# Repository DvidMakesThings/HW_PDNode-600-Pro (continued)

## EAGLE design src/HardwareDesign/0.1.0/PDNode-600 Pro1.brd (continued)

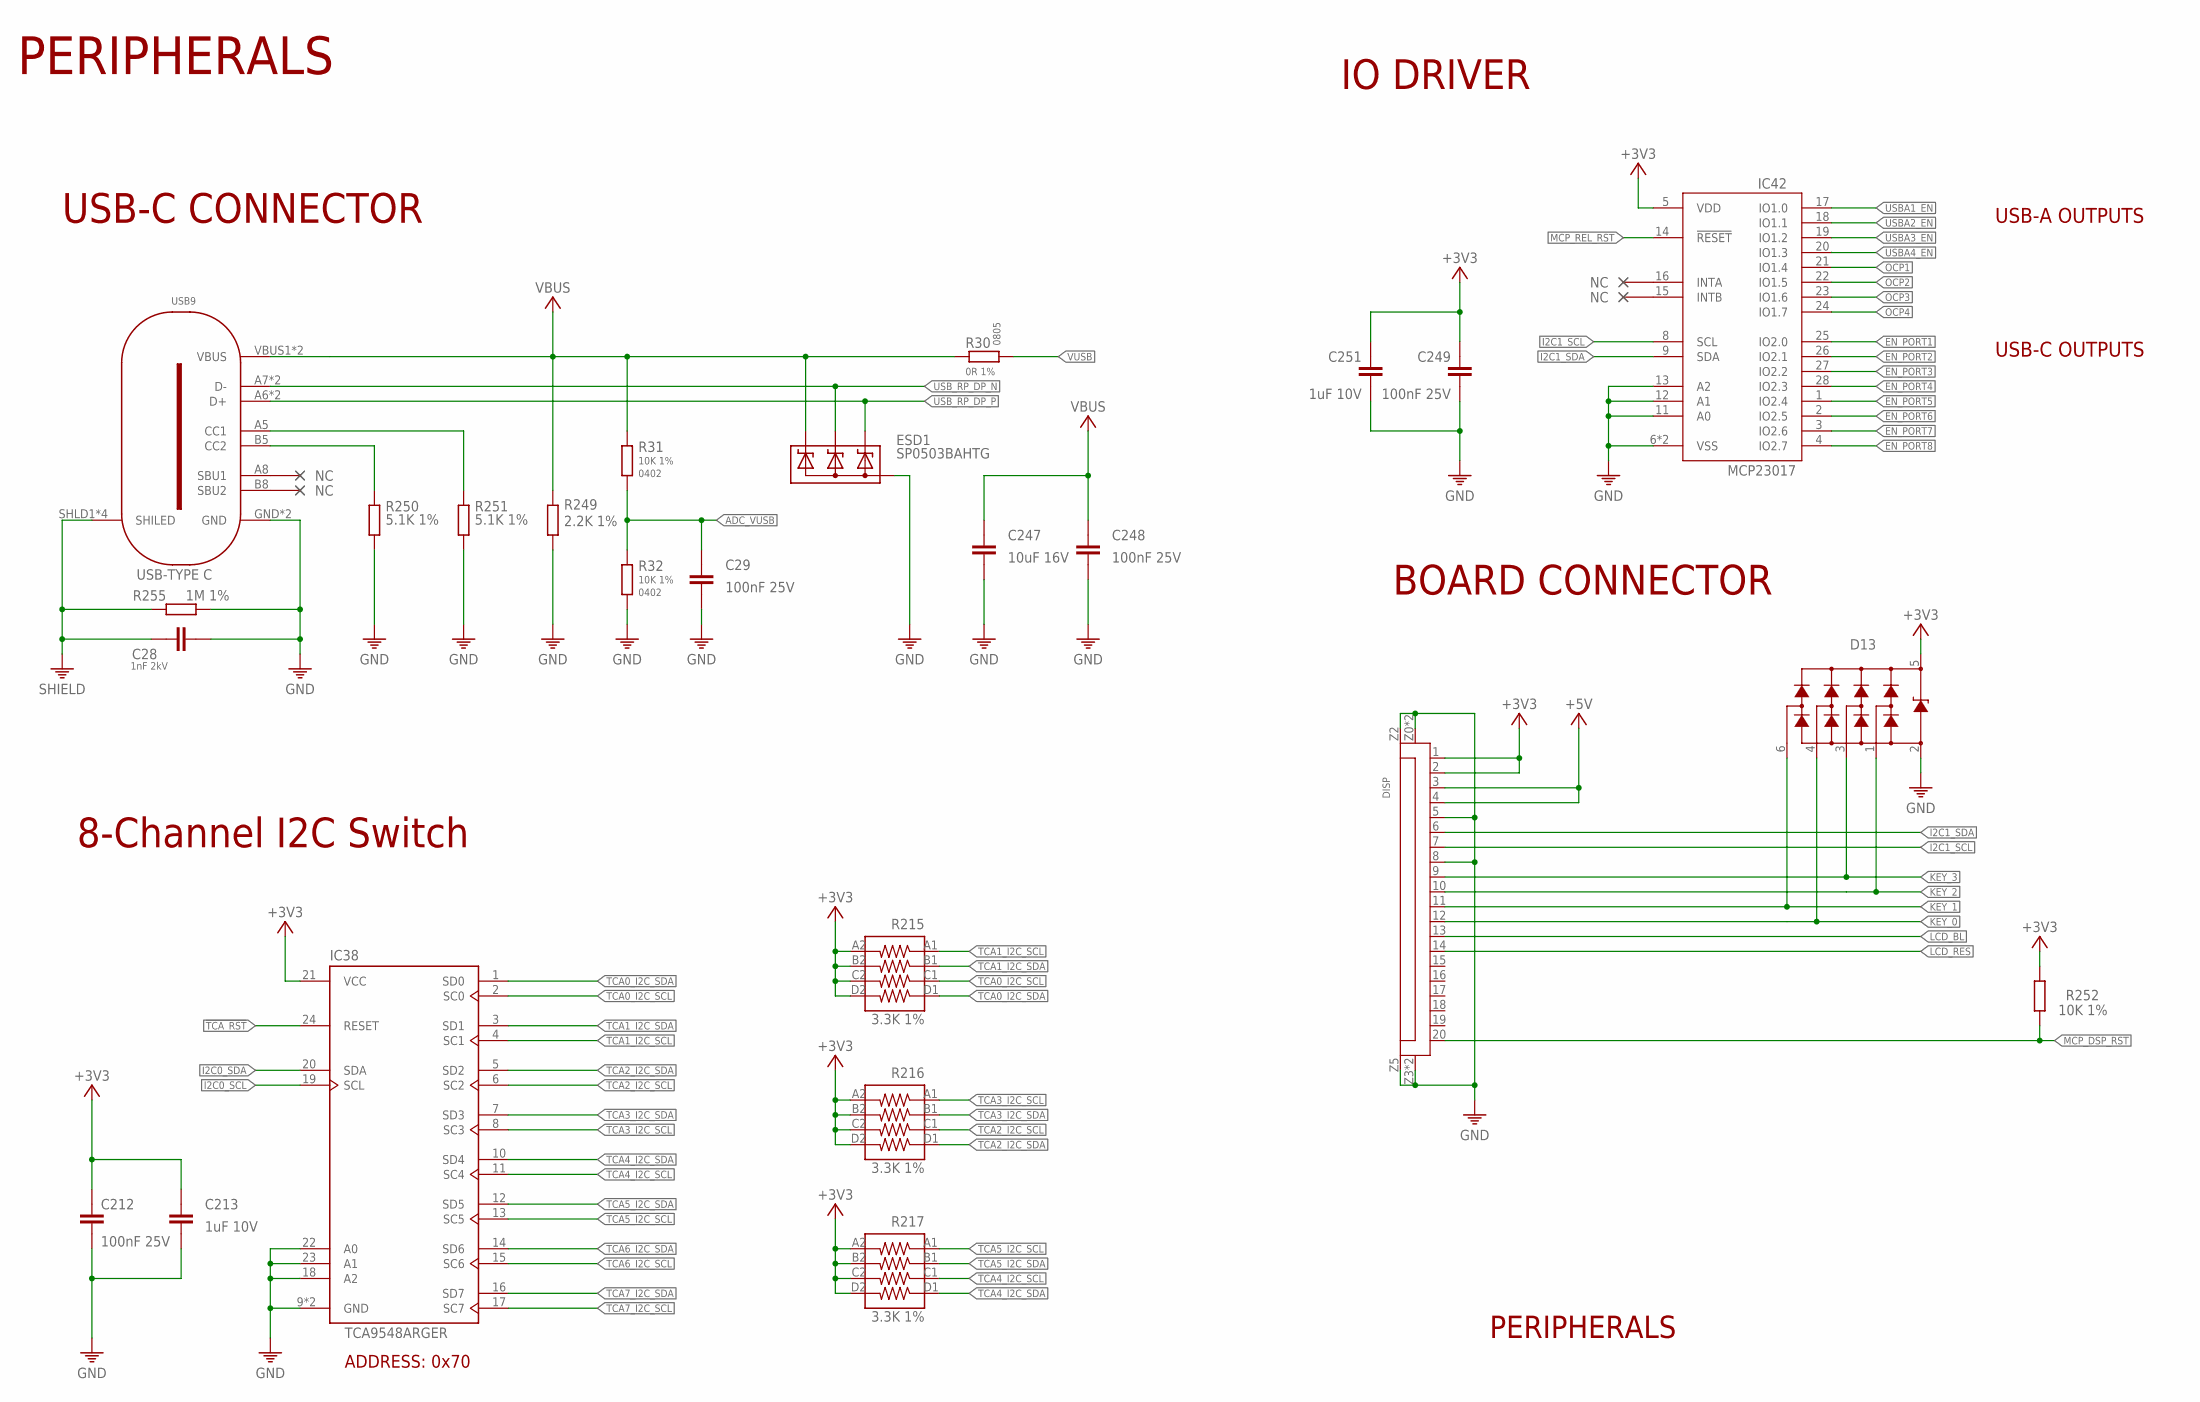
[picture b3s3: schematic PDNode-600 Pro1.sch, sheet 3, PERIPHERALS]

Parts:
C28: 1nF 2kV; 1206
C29, C248: 100nF 25V; 0402
C212, C249: 100nF 25V; 0201
C213, C251: 1uF 10V; 0201
C247: 10uF 16V; 0603
D13: HDMIULC6-4SC6Y; SOT23-6
DISP: AFC11-S20ICC-00; FPC20
ESD1: SP0503BAHTG; SOT143
IC38: TCA9548ARGER; QFN50P400X400X100-25T210N
IC42: MCP23017T-E/ML; QFN28[6X6]ML
R30: 0R 1%; 0805
R31, R32: 10K 1%; 0402
R215, R216, R217: 3.3K 1%; _0603X4-1206
R249: 2.2K 1%; 0201
R250, R251: 5.1K 1%; 0201
R252: 10K 1%; 0201
R255: 1M 1%; 1206
USB9: USB-TYPE-C-018; USB-C

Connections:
!TCA_RST: IC38.24 (RESET)
+3V3: C212.1, C213.1, C249.1, C251.1, D13.5, DISP.1, DISP.2, IC38.21 (VCC), IC42.5 (VDD), R215.A2 (8), R215.B2 (7), R215.C2 (6), R215.D2 (5), R216.A2 (8), R216.B2 (7), R216.C2 (6), R216.D2 (5), R217.A2 (8), R217.B2 (7), R217.C2 (6), R217.D2 (5), R252.2; also elsewhere on the board
+5V: DISP.3, DISP.4
ADC_VUSB: C29.1, R31.2, R32.1
CC1: R251.1, USB9.A5 (CC1)
CC2: R250.1, USB9.B5 (CC2)
EN_PORT1: IC42.25 (IO2.0); also elsewhere on the board
EN_PORT2: IC42.26 (IO2.1); also elsewhere on the board
EN_PORT3: IC42.27 (IO2.2); also elsewhere on the board
EN_PORT4: IC42.28 (IO2.3); also elsewhere on the board
EN_PORT5: IC42.1 (IO2.4); also elsewhere on the board
EN_PORT6: IC42.2 (IO2.5); also elsewhere on the board
EN_PORT7: IC42.3 (IO2.6); also elsewhere on the board
EN_PORT8: IC42.4 (IO2.7); also elsewhere on the board
GND: C28.2, C29.2, C212.2, C213.2, C247.2, C248.2, C249.2, C251.2, D13.2, DISP.5, DISP.8, DISP.Z0 (Z1), DISP.Z1, DISP.Z2, DISP.Z3, DISP.Z4 (Z3), DISP.Z5 (Z4), ESD1.1 (A), IC38.9 (GND), IC38.18 (A2), IC38.22 (A0), IC38.23 (A1), IC38.25 (GND), IC42.6 (VSS), IC42.11 (A0), IC42.12 (A1), IC42.13 (A2), IC42.PAD (VSS), R32.2, R249.2, R250.2, R251.2, R255.2, USB9.GND, USB9.GND2 (GND); also elsewhere on the board
I2C0_SCL: IC38.19 (SCL); also elsewhere on the board
I2C0_SDA: IC38.20 (SDA); also elsewhere on the board
I2C1_SCL: DISP.7, IC42.8 (SCL); also elsewhere on the board
I2C1_SDA: DISP.6, IC42.9 (SDA); also elsewhere on the board
KEY_0: D13.4, DISP.12; also elsewhere on the board
KEY_1: D13.6, DISP.11; also elsewhere on the board
KEY_2: D13.1, DISP.10; also elsewhere on the board
KEY_3: D13.3, DISP.9; also elsewhere on the board
LCD_BL: DISP.13
LCD_RES: DISP.14
MCP_DSP_RST: DISP.20, R252.1
MCP_REL_RST: IC42.14 (!RESET)
OCP1: IC42.21 (IO1.4); also elsewhere on the board
OCP2: IC42.22 (IO1.5); also elsewhere on the board
OCP3: IC42.23 (IO1.6); also elsewhere on the board
OCP4: IC42.24 (IO1.7); also elsewhere on the board
SHIELD: C28.1, R255.1, USB9.SHLD1 (SHILED), USB9.SHLD2 (SHILED), USB9.SHLD3 (SHILED), USB9.SHLD4 (SHILED); also elsewhere on the board
TCA0_I2C_SCL: IC38.2 (SC0), R215.C1 (3); also elsewhere on the board
TCA0_I2C_SDA: IC38.1 (SD0), R215.D1 (4); also elsewhere on the board
TCA1_I2C_SCL: IC38.4 (SC1), R215.A1 (1); also elsewhere on the board
TCA1_I2C_SDA: IC38.3 (SD1), R215.B1 (2); also elsewhere on the board
TCA2_I2C_SCL: IC38.6 (SC2), R216.C1 (3); also elsewhere on the board
TCA2_I2C_SDA: IC38.5 (SD2), R216.D1 (4); also elsewhere on the board
TCA3_I2C_SCL: IC38.8 (SC3), R216.A1 (1); also elsewhere on the board
TCA3_I2C_SDA: IC38.7 (SD3), R216.B1 (2); also elsewhere on the board
TCA4_I2C_SCL: IC38.11 (SC4), R217.C1 (3); also elsewhere on the board
TCA4_I2C_SDA: IC38.10 (SD4), R217.D1 (4); also elsewhere on the board
TCA5_I2C_SCL: IC38.13 (SC5), R217.A1 (1); also elsewhere on the board
TCA5_I2C_SDA: IC38.12 (SD5), R217.B1 (2); also elsewhere on the board
TCA6_I2C_SCL: IC38.15 (SC6)
TCA6_I2C_SDA: IC38.14 (SD6)
TCA7_I2C_SCL: IC38.17 (SC7)
TCA7_I2C_SDA: IC38.16 (SD7)
USBA1_EN: IC42.17 (IO1.0); also elsewhere on the board
USBA2_EN: IC42.18 (IO1.1); also elsewhere on the board
USBA3_EN: IC42.19 (IO1.2); also elsewhere on the board
USBA4_EN: IC42.20 (IO1.3); also elsewhere on the board
USB_RP_DP_N: ESD1.3 (C2), USB9.A7 (D-), USB9.B7 (D-); also elsewhere on the board
USB_RP_DP_P: ESD1.2 (C1), USB9.A6 (D+), USB9.B6 (D+); also elsewhere on the board
VBUS: C247.1, C248.1, ESD1.4 (C3), R30.1, R31.1, R249.1, USB9.VBUS1 (VBUS), USB9.VBUS2 (VBUS)
VUSB: R30.2

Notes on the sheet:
PERIPHERALS
USB-C CONNECTOR
8-Channel I2C Switch
ADDRESS: 0x70
IO DRIVER
USB-A OUTPUTS
USB-C OUTPUTS
BOARD CONNECTOR

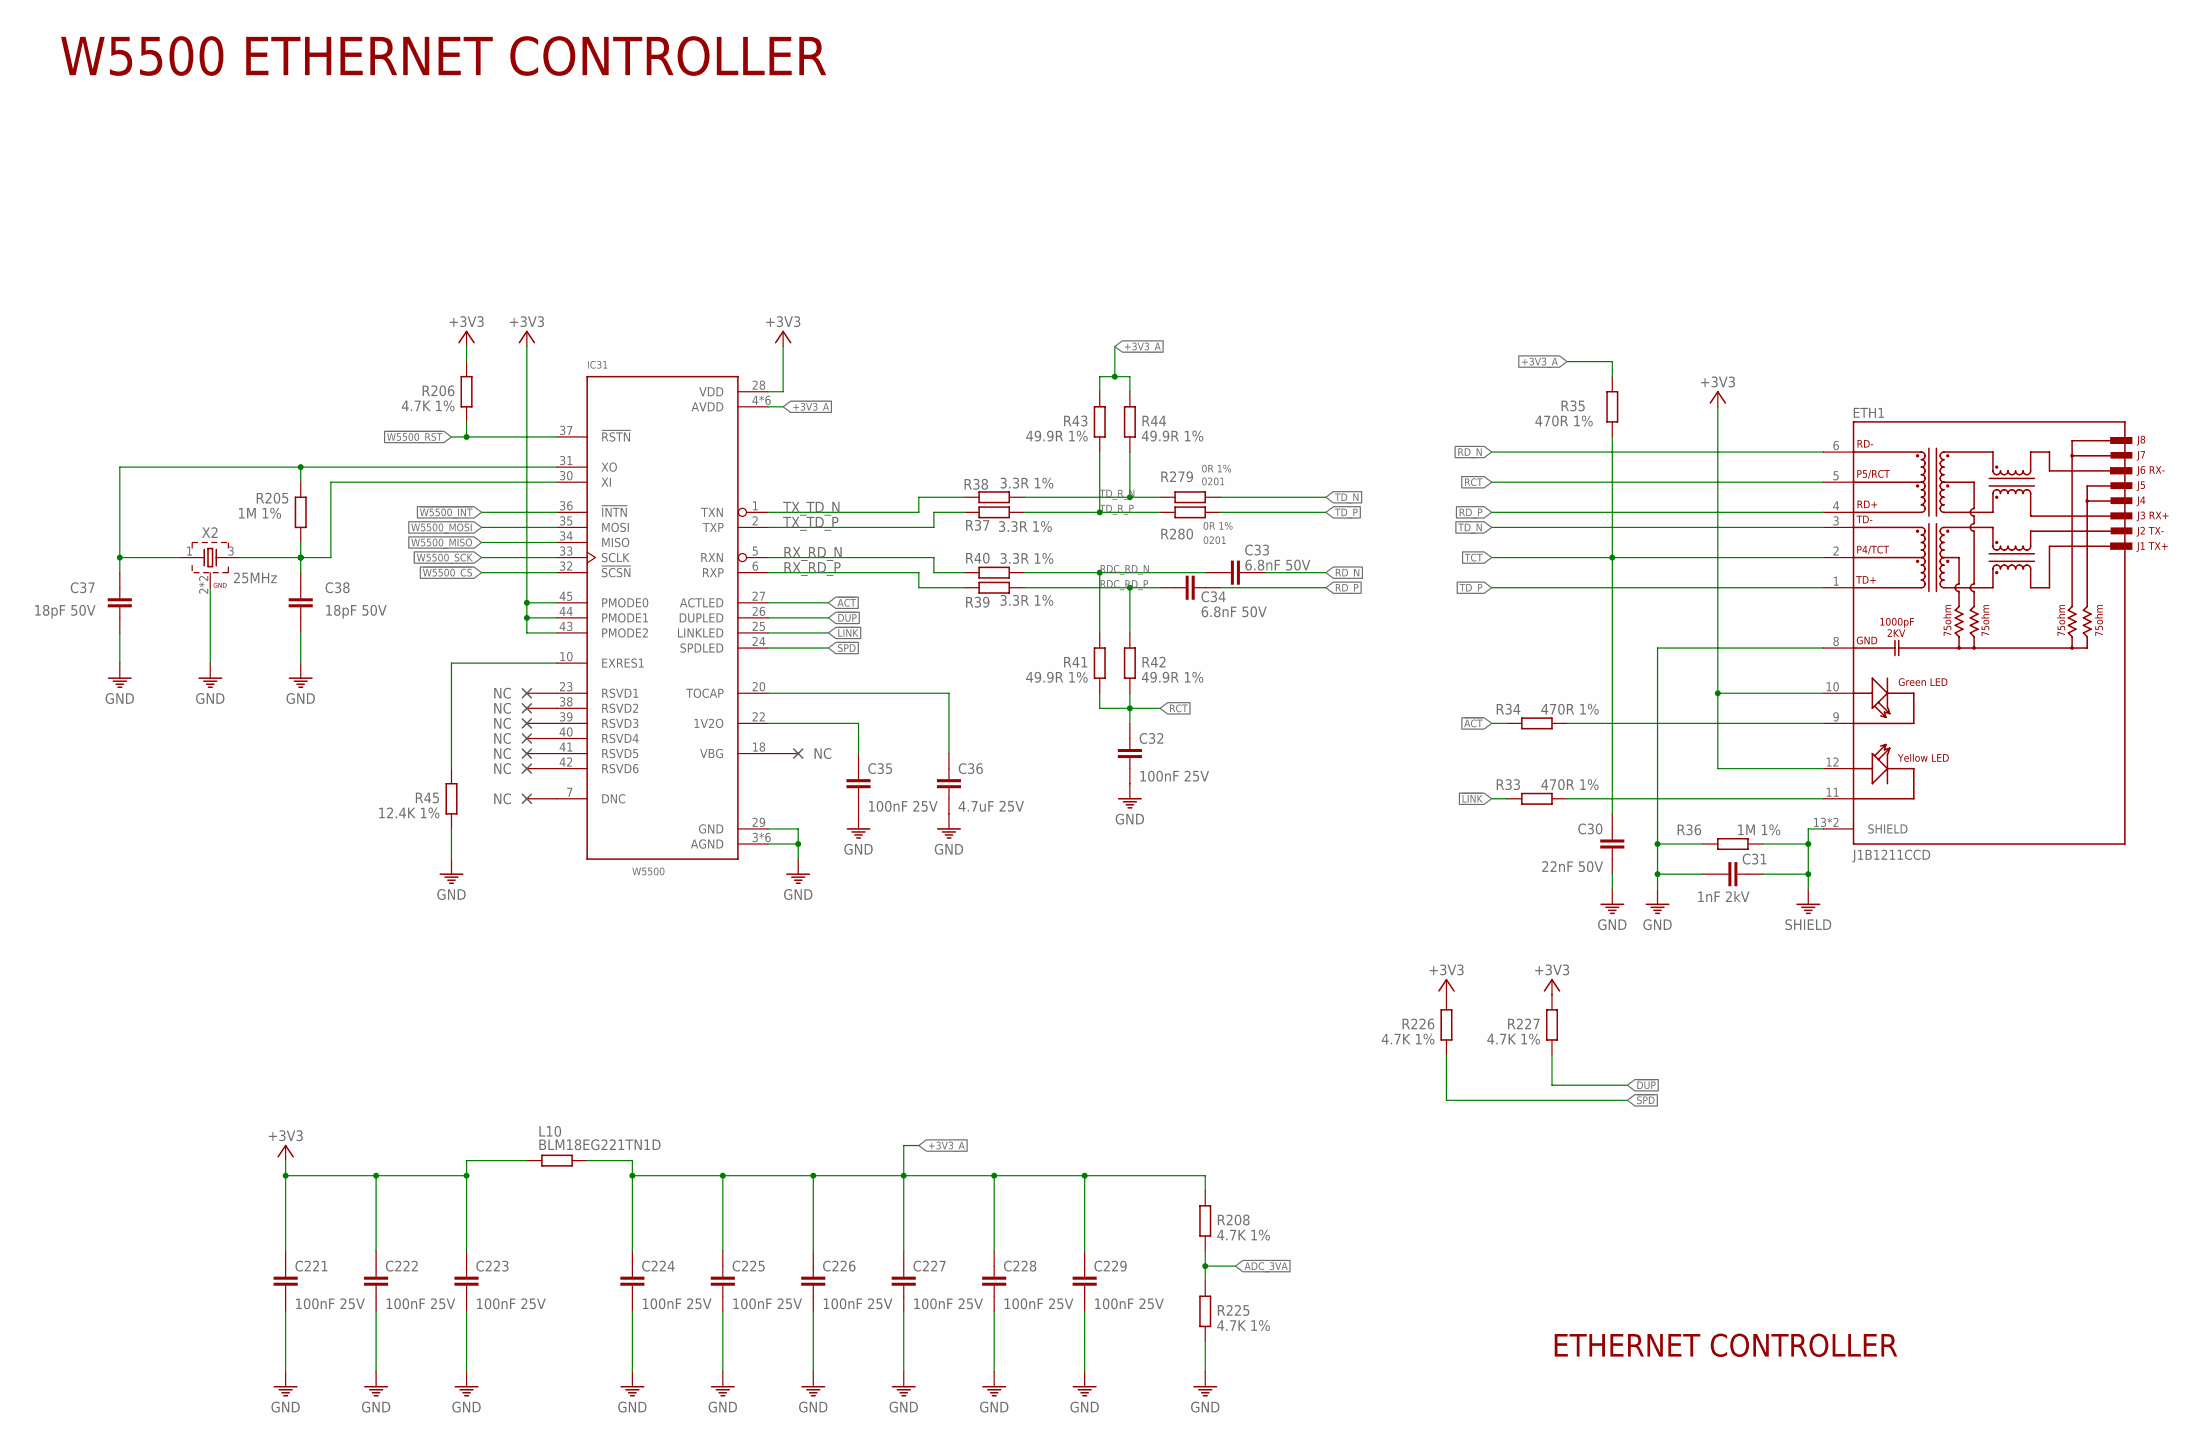
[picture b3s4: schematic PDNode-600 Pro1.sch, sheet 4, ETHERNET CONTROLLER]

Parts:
C30: 22nF 50V; 0402
C31: 1nF 2kV; 1206
C32: 100nF 25V; 0402
C33, C34: 6.8nF 50V; 0201
C35, C221, C222, C223, C224, C225, C226, C227, C228, C229: 100nF 25V; 0201
C36: 4.7uF 25V; 0402
C37, C38: 18pF 50V; 0201
ETH1: J1B1211CCD
IC31: W5500; LQFP48
L10: BLM18EG221TN1D; 0603
R33, R34, R35: 470R 1%; 0402
R36: 1M 1%; 1206
R37, R38, R39, R40: 3.3R 1%; 0201
R41, R42, R43, R44: 49.9R 1%; 0201
R45: 12.4K 1%; R0201
R205: 1M 1%; 0201
R206, R208, R225, R226, R227: 4.7K 1%; 0201
R279, R280: 0R 1%; 0201
X2: 25MHz; WE-XTAL_CFPX-180

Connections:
!ACT: IC31.27 (ACTLED), R34.1
!DUP: IC31.26 (DUPLED), R227.1
!LINK: IC31.25 (LINKLED), R33.1
!SPD: IC31.24 (SPDLED), R226.1
!W5500_CS: IC31.32 (!SCSN); also elsewhere on the board
!W5500_INT: IC31.36 (!INTN); also elsewhere on the board
!W5500_RST: IC31.37 (!RSTN), R206.1; also elsewhere on the board
+3V3: C221.1, C222.1, C223.1, ETH1.10 (GREEN+), ETH1.12 (YELLOW+), IC31.28 (VDD), IC31.43 (PMODE2), IC31.44 (PMODE1), IC31.45 (PMODE0), L10.1, R206.2, R226.2, R227.2; also elsewhere on the board
+3V3_A: C224.1, C225.1, C226.1, C227.1, C228.1, C229.1, IC31.4 (AVDD), IC31.8 (AVDD), IC31.11 (AVDD), IC31.15 (AVDD), IC31.17 (AVDD), IC31.21 (AVDD), L10.2, R35.2, R43.2, R44.2, R208.2
ADC_3VA: R208.1, R225.2
GND: C30.2, C31.1, C32.2, C35.2, C36.2, C37.2, C38.2, C221.2, C222.2, C223.2, C224.2, C225.2, C226.2, C227.2, C228.2, C229.2, ETH1.8 (GND), IC31.3 (AGND), IC31.9 (AGND), IC31.14 (AGND), IC31.16 (AGND), IC31.19 (AGND), IC31.29 (GND), IC31.48 (AGND), R36.1, R45.1, R225.1, X2.2 (GND), X2.4 (GND); also elsewhere on the board
unnamed: ETH1.11 (YELLOW-), R33.2
unnamed: ETH1.9 (GREEN-), R34.2
unnamed: IC31.10 (EXRES1), R45.2
unnamed: C35.1, IC31.22 (1V2O)
unnamed: C36.1, IC31.20 (TOCAP)
unnamed: C38.1, IC31.30 (XI), R205.1, X2.3 (2)
RCT: C32.1, ETH1.5 (P5/RCT), R41.1, R42.1
RDC_RD_N: C33.1, R40.2, R41.2
RDC_RD_P: C34.1, R39.2, R42.2
RD_N: C33.2, ETH1.6 (RD-)
RD_P: C34.2, ETH1.4 (RD+)
RX_RD_N: IC31.5 (RXN), R40.1
RX_RD_P: IC31.6 (RXP), R39.1
SHIELD: C31.2, ETH1.13 (SHIELD), ETH1.14 (SHIELD), R36.2; also elsewhere on the board
TCT: C30.1, ETH1.2 (P4/TCT), R35.1
TD_N: ETH1.3 (TD-), R279.2
TD_P: ETH1.1 (TD+), R280.2
TD_R_N: R38.2, R44.1, R279.1
TD_R_P: R37.2, R43.1, R280.1
TX_TD_N: IC31.1 (TXN), R38.1
TX_TD_P: IC31.2 (TXP), R37.1
W5500_MISO: IC31.34 (MISO); also elsewhere on the board
W5500_MOSI: IC31.35 (MOSI); also elsewhere on the board
W5500_SCK: IC31.33 (SCLK); also elsewhere on the board
XO: C37.1, IC31.31 (XO), R205.2, X2.1

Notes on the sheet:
W5500 ETHERNET CONTROLLER
ETHERNET CONTROLLER

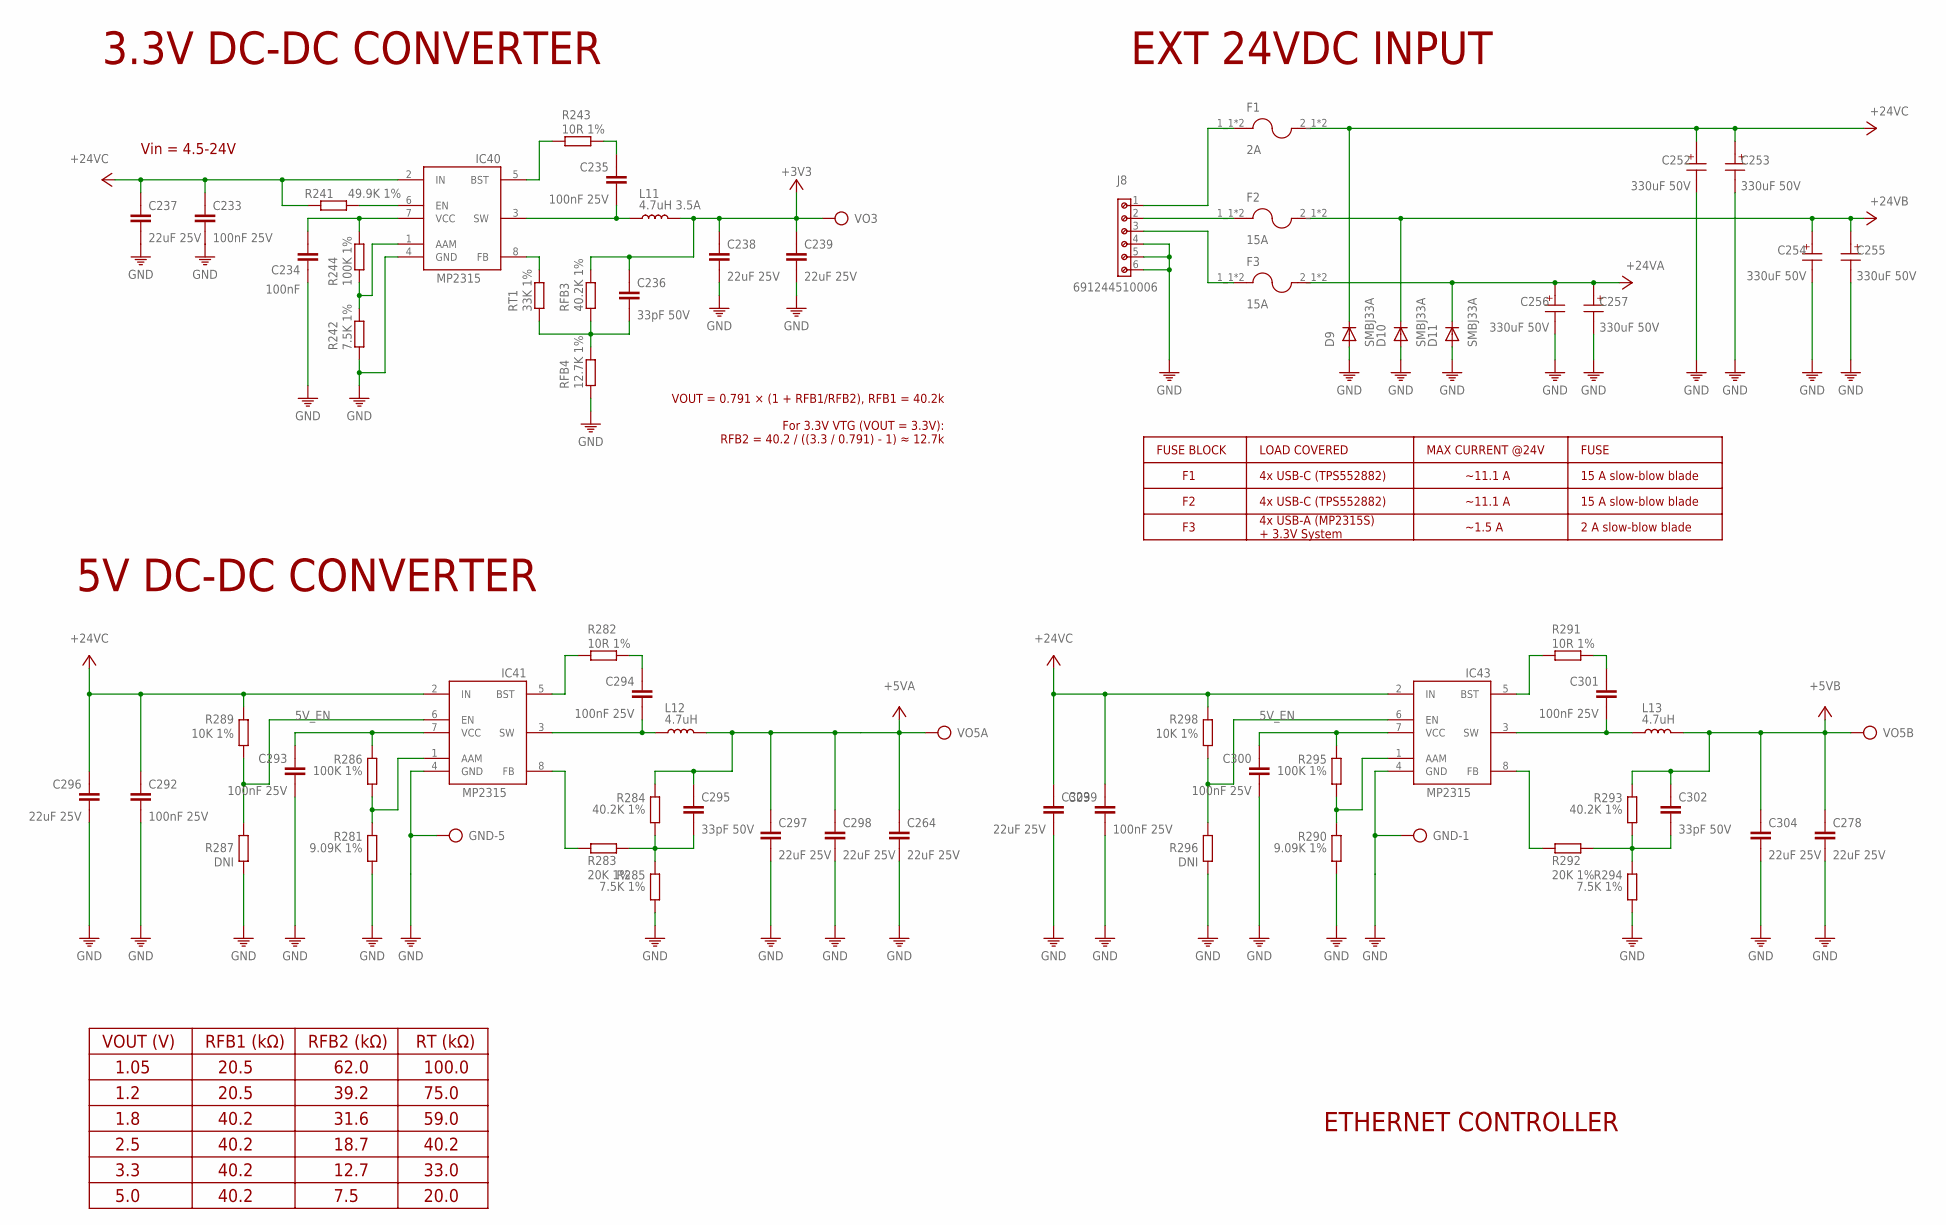
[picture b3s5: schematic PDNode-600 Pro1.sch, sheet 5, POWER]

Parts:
C233, C235: 100nF 25V; 0201
C234: 100nF; 0201
C236: 33pF 50V; 0201
C237, C238, C239, C264, C278, C296, C297, C298, C303, C304: 22uF 25V; 1206
C252, C253, C254, C255, C256, C257: 330uF 50V; 10X10.5(DXL)
C292, C293, C294, C299, C300, C301: 100nF 25V; 0402
C295, C302: 33pF 50V; 0402
D9, D10, D11: SMBJ33A; SMB
F1: 2A; FUSE_3544-2
F2, F3: 15A; FUSE_3544-2
GND-1, GND-5: DNI; TP-ROUND
IC40, IC41, IC43: MP2315GJ-Z; SOT65P280X110-8N
J8: 691244510006
L11: 4.7uH 3.5A; SRR5228A
L12, L13: 4.7uH; SRR5228A
R241: 49.9K 1%; 0201
R242: 7.5K 1%; 0201
R243: 10R 1%; 0201
R244: 100K 1%; 0201
R281, R290: 9.09K 1%; 0402
R282, R291: 10R 1%; 0402
R283, R292: 20K 1%; 0402
R284, R293: 40.2K 1%; 0402
R285, R294: 7.5K 1%; 0402
R286, R295: 100K 1%; 0402
R287, R296: DNI; 0402
R289, R298: 10K 1%; 0402
RFB3: 40.2K 1%; 0201
RFB4: 12.7K 1%; 0201
RT1: 33K 1%; 0201
VO3, VO5A, VO5B: DNI; TP-ROUND

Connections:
3V3_EN_SYS1: IC40.6 (EN), R241.2
5VFB: C295.2, R283.2, R284.2, R285.1
5VFB1: C302.2, R292.2, R293.2, R294.1
5V_EN: IC41.6 (EN), IC43.6 (EN), R287.2, R289.1, R296.2, R298.1
24VINA: F2.1_1 (1), F2.1_2 (1), J8.2
24VINB: F3.1_1 (1), F3.1_2 (1), J8.3
24VINC: F1.1_1 (1), F1.1_2 (1), J8.1
+3V3: C236.1, C238.1, C239.1, L11.2, RFB3.1, VO3.TP; also elsewhere on the board
+5VA: C264.1, C295.1, C297.1, C298.1, L12.2, R284.1, VO5A.TP; also elsewhere on the board
+5VB: C278.1, C302.1, C304.1, L13.2, R293.1, VO5B.TP; also elsewhere on the board
+24V_A: C256.1 (+), C257.1 (+), D11.C, F3.2_1 (2), F3.2_2 (2); also elsewhere on the board
+24V_B: C254.1 (+), C255.1 (+), D10.C, F2.2_1 (2), F2.2_2 (2); also elsewhere on the board
+24V_C: C233.1, C237.1, C252.1 (+), C253.1 (+), C292.1, C296.1, C299.1, C303.1, D9.C, F1.2_1 (2), F1.2_2 (2), IC40.2 (IN), IC41.2 (IN), IC43.2 (IN), R241.1, R289.2, R298.2
GND: C233.2, C234.2, C237.2, C238.2, C239.2, C252.2 (-), C253.2 (-), C254.2 (-), C255.2 (-), C256.2 (-), C257.2 (-), C264.2, C278.2, C292.2, C293.2, C296.2, C297.2, C298.2, C299.2, C300.2, C303.2, C304.2, D9.A, D10.A, D11.A, GND-1.TP, GND-5.TP, IC40.4 (GND), IC41.4 (GND), IC43.4 (GND), J8.4, J8.5, J8.6, R242.2, R281.2, R285.2, R287.1, R290.2, R294.2, R296.1, RFB4.2; also elsewhere on the board
unnamed: IC41.5 (BST), R282.2
unnamed: IC41.8 (FB), R283.1
unnamed: C294.1, R282.1
unnamed: C293.1, IC41.7 (VCC), R286.1
unnamed: IC41.1 (AAM), R281.1, R286.2
unnamed: IC43.5 (BST), R291.2
unnamed: IC43.8 (FB), R292.1
unnamed: C301.1, R291.1
unnamed: C300.1, IC43.7 (VCC), R295.1
unnamed: IC43.1 (AAM), R290.1, R295.2
unnamed: IC40.5 (BST), R243.2
unnamed: IC40.8 (FB), RT1.1
unnamed: C235.1, R243.1
unnamed: C236.2, RFB3.2, RFB4.1, RT1.2
unnamed: C234.1, IC40.7 (VCC), R244.1
unnamed: IC40.1 (AAM), R242.1, R244.2
SW1: C301.2, IC43.3 (SW), L13.1
SW3: C235.2, IC40.3 (SW), L11.1
SW5: C294.2, IC41.3 (SW), L12.1

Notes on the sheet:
VOUT = 0.791 × (1 + RFB1/RFB2), RFB1 = 40.2k For 3.3V VTG (VOUT = 3.3V): RFB2 = 40.2 / ((3.3 / 0.791) - 1) ≈ 12.7k
VOUT (V)
EXT 24VDC INPUT
FUSE BLOCK
LOAD COVERED
MAX CURRENT @24V
FUSE
4x USB-C (TPS552882)
4x USB-A (MP2315S) + 3.3V System
~11.1 A
~1.5 A
15 A slow-blow blade
2 A slow-blow blade
RFB1 (kΩ)
RFB2 (kΩ)
RT (kΩ)
1.05
1.2
1.8
3.3
5.0
20.5
40.2
62.0
39.2
31.6
18.7
12.7
7.5
2.5
100.0
75.0
59.0
33.0
20.0
3.3V DC-DC CONVERTER
Vin = 4.5-24V
5V DC-DC CONVERTER
ETHERNET CONTROLLER

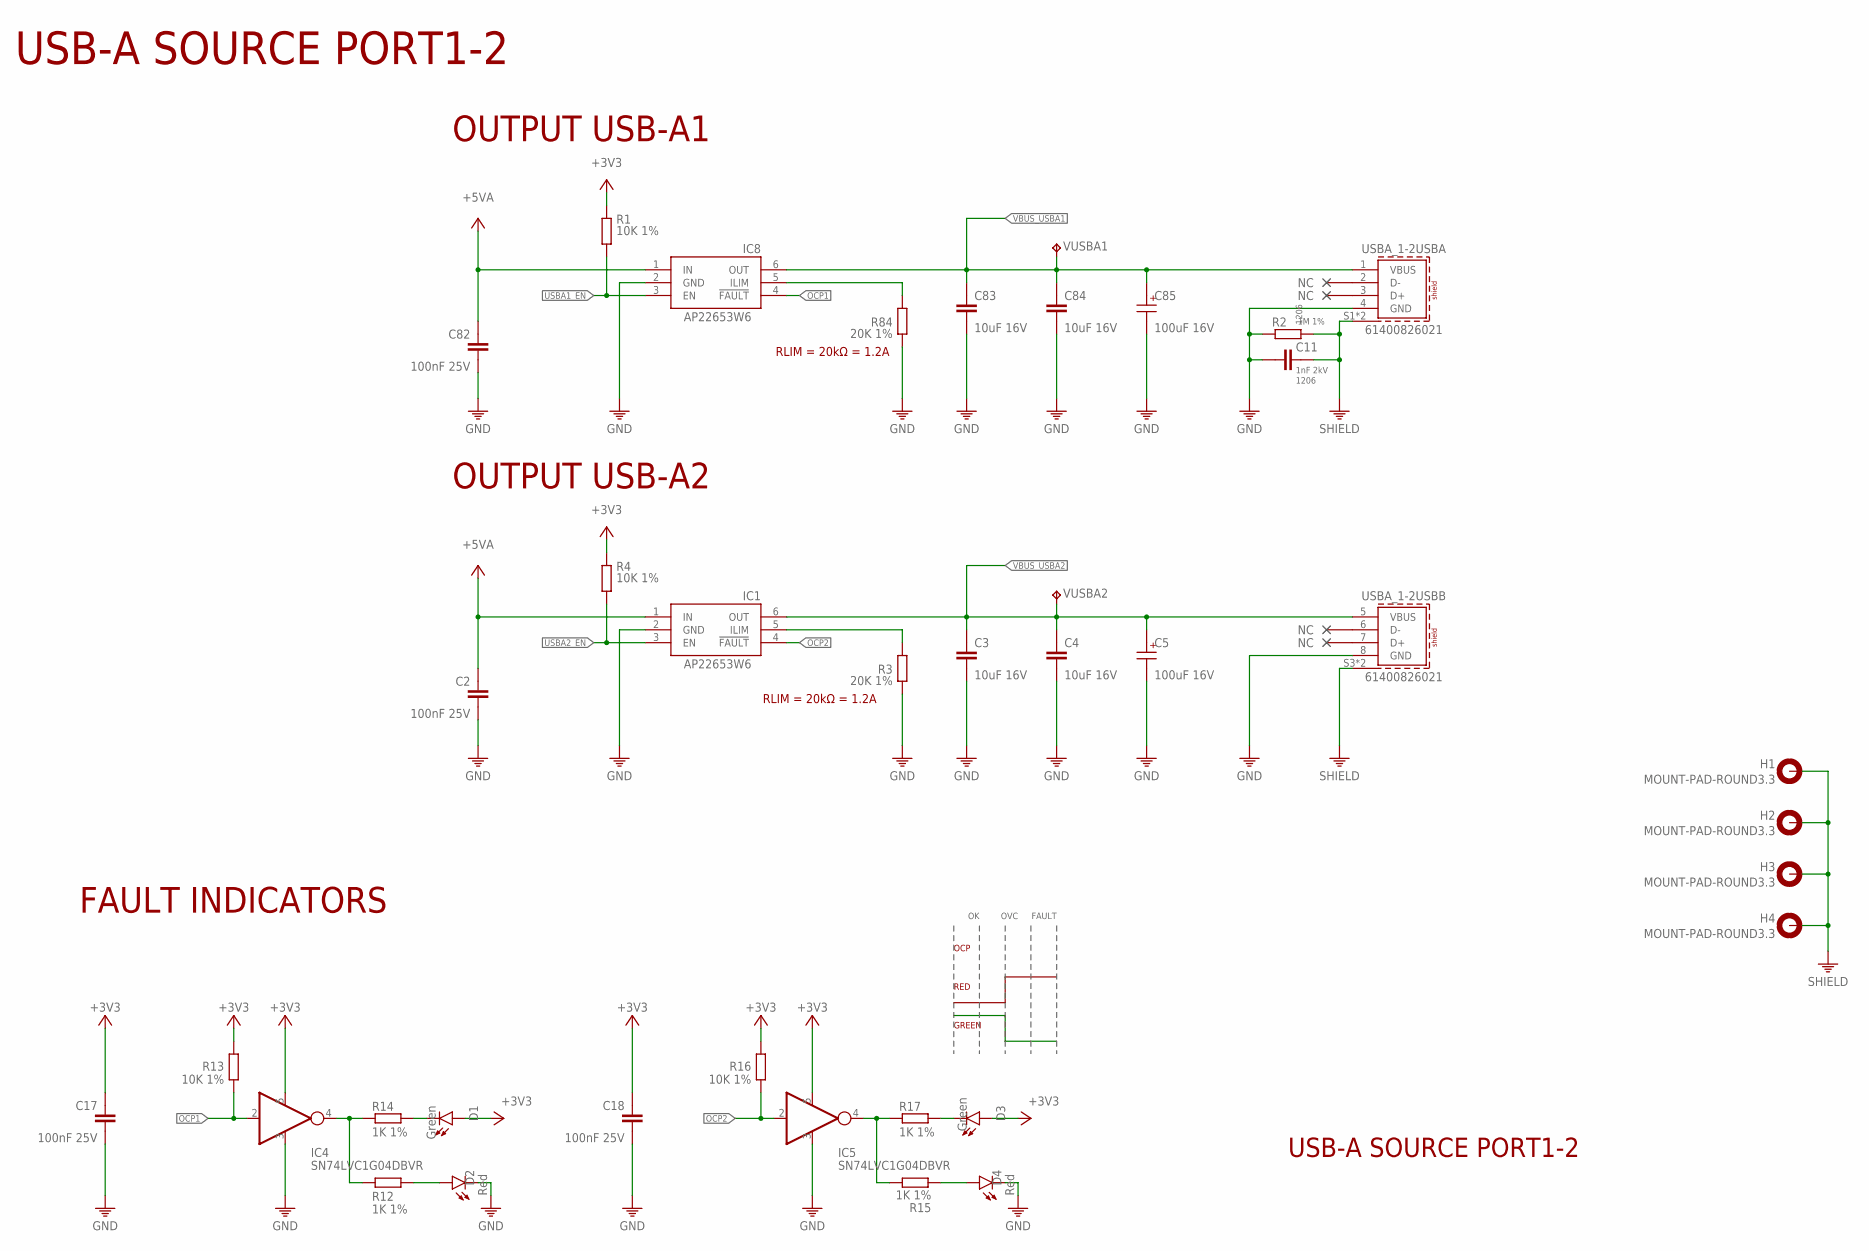
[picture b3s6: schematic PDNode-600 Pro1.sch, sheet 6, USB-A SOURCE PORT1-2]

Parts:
C2, C17, C18, C82: 100nF 25V; 0201
C3, C4, C83, C84: 10uF 16V; 0603
C5, C85: 100uF 16V; 5X5.5(DXL)
C11: 1nF 2kV; 1206
D1, D3: Green; LED-0603
D2, D4: Red; LED-0603
H1, H2, H3, H4: MOUNT-PAD-ROUND3.3; 3,3-PAD
IC1, IC8: AP22653W6; SOT23-6
IC4, IC5: SN74LVC1G04DBVR; SOT95P280X145-5N
R1, R4: 10K 1%; 0201
R2: 1M 1%; 1206
R3, R84: 20K 1%; 0201
R12, R14, R15, R17: 1K 1%; 0402
R13, R16: 10K 1%; 0402
USBA_1-2: 61400826021
VUSBA1, VUSBA2: TPB1,27; B1,27

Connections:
+3V3: C17.1, C18.1, D1.A, D3.A, IC4.5 (V+), IC5.5 (V+), R1.1, R4.1, R13.2, R16.2; also elsewhere on the board
+5VA: C2.1, C82.1, IC1.1 (IN), IC8.1 (IN); also elsewhere on the board
GND: C2.2, C3.2, C4.2, C5.2 (-), C11.2, C17.2, C18.2, C82.2, C83.2, C84.2, C85.2 (-), D2.C, D4.C, IC1.2 (GND), IC4.3 (V-), IC5.3 (V-), IC8.2 (GND), R2.1, R3.2, R84.2, USBA_1-2.4 (GND), USBA_1-2.8 (GND); also elsewhere on the board
unnamed: IC1.5 (ILIM), R3.1
unnamed: D2.A, R12.2
unnamed: IC4.4 (OUT), R12.1, R14.1
unnamed: D1.C, R14.2
unnamed: D4.A, R15.1
unnamed: IC5.4 (OUT), R15.2, R17.1
unnamed: D3.C, R17.2
unnamed: IC8.5 (ILIM), R84.1
OCP1: IC4.2 (IN), IC8.4 (!FAULT), R13.1; also elsewhere on the board
OCP2: IC1.4 (!FAULT), IC5.2 (IN), R16.1; also elsewhere on the board
SHIELD: C11.1, H1.B3,3, H2.B3,3, H3.B3,3, H4.B3,3, R2.2, USBA_1-2.S1 (SHIELD), USBA_1-2.S2 (SHIELD), USBA_1-2.S3 (SHIELD), USBA_1-2.S4 (SHIELD); also elsewhere on the board
USBA1_EN: IC8.3 (EN), R1.2; also elsewhere on the board
USBA2_EN: IC1.3 (EN), R4.2; also elsewhere on the board
VBUS_USBA1: C83.1, C84.1, C85.1 (+), IC8.6 (OUT), USBA_1-2.1 (VBUS), VUSBA1.TP
VBUS_USBA2: C3.1, C4.1, C5.1 (+), IC1.6 (OUT), USBA_1-2.5 (VBUS), VUSBA2.TP

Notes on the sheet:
OUTPUT USB-A1
RLIM = 20kΩ = 1.2A
OUTPUT USB-A2
FAULT INDICATORS
USB-A SOURCE PORT1-2
OCP
RED
GREEN
OVC
FAULT

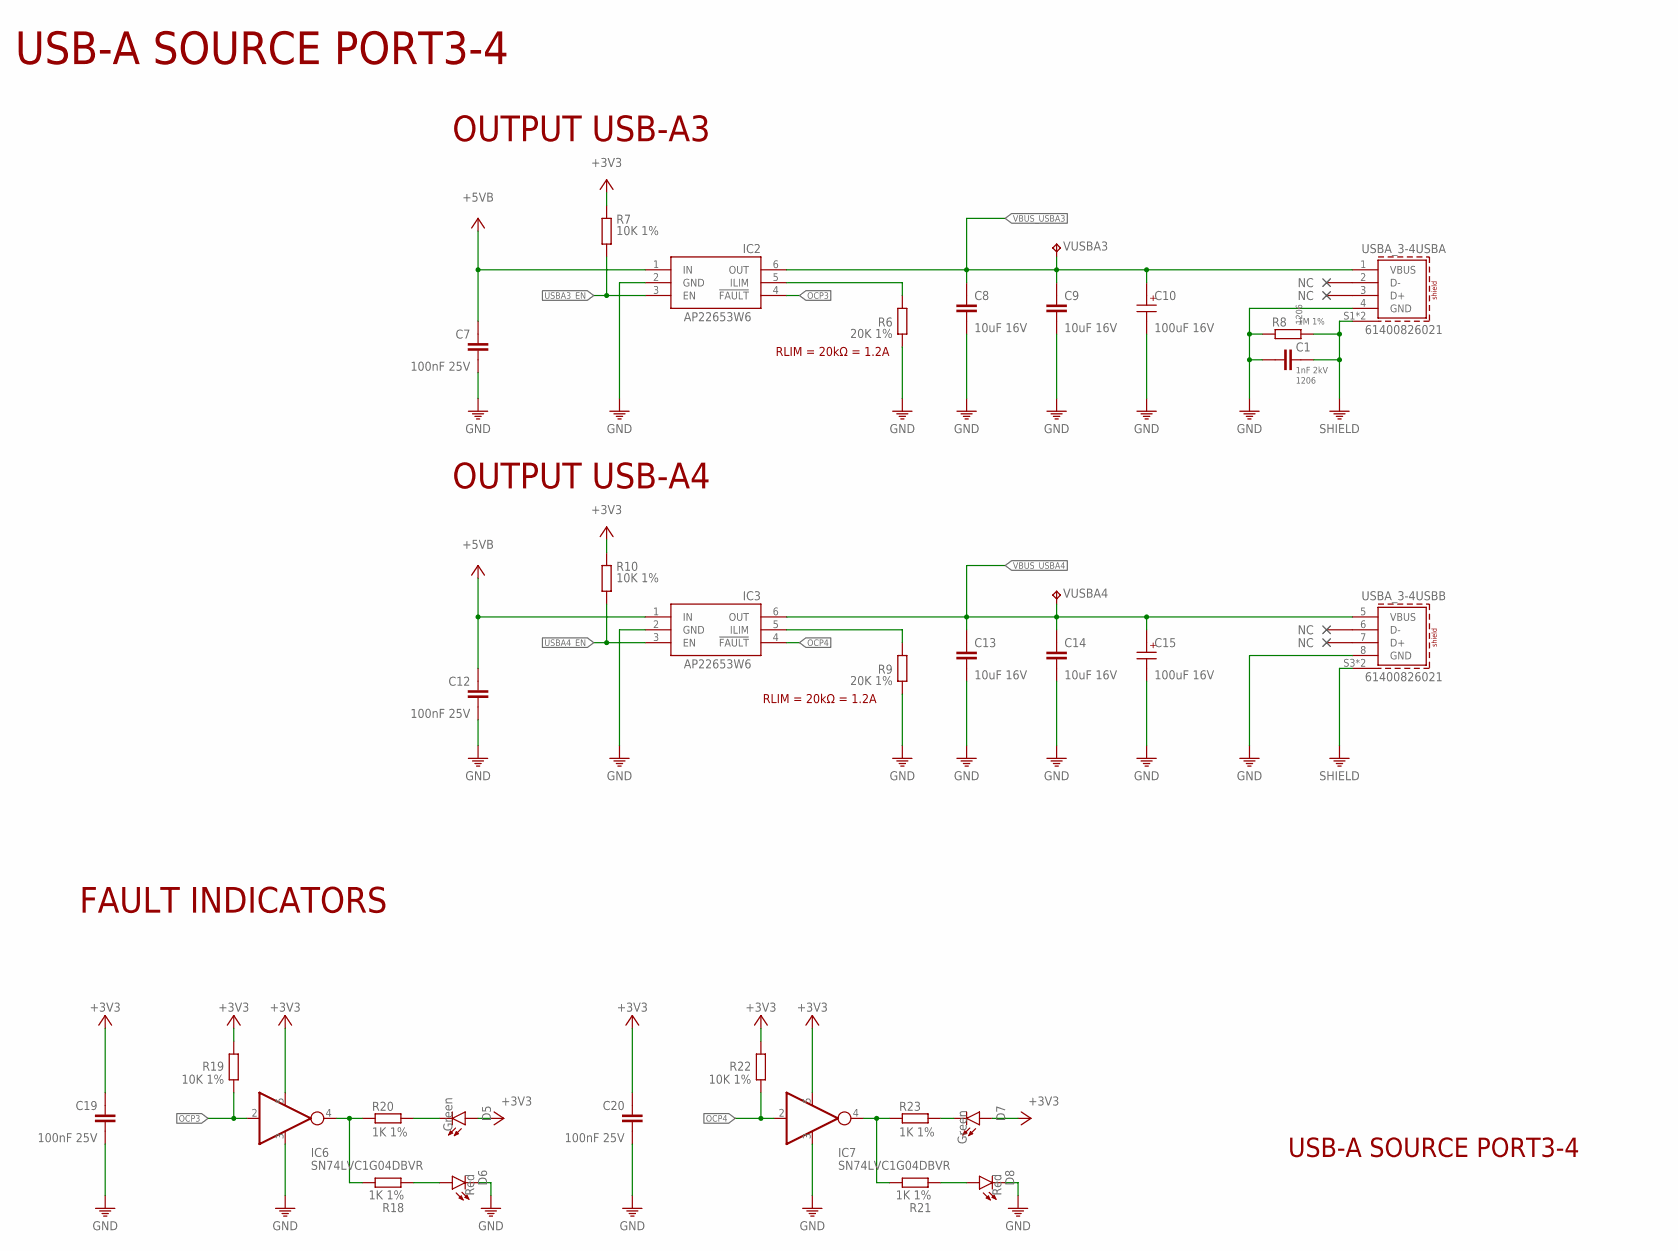
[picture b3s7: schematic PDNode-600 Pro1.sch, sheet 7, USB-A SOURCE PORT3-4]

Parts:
C1: 1nF 2kV; 1206
C7, C12, C19, C20: 100nF 25V; 0201
C8, C9, C13, C14: 10uF 16V; 0603
C10, C15: 100uF 16V; 5X5.5(DXL)
D5, D7: Green; LED-0603
D6, D8: Red; LED-0603
IC2, IC3: AP22653W6; SOT23-6
IC6, IC7: SN74LVC1G04DBVR; SOT95P280X145-5N
R6, R9: 20K 1%; 0201
R7, R10: 10K 1%; 0201
R8: 1M 1%; 1206
R18, R20, R21, R23: 1K 1%; 0402
R19, R22: 10K 1%; 0402
USBA_3-4: 61400826021
VUSBA3, VUSBA4: TPB1,27; B1,27

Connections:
+3V3: C19.1, C20.1, D5.A, D7.A, IC6.5 (V+), IC7.5 (V+), R7.1, R10.1, R19.2, R22.2; also elsewhere on the board
+5VB: C7.1, C12.1, IC2.1 (IN), IC3.1 (IN); also elsewhere on the board
GND: C1.2, C7.2, C8.2, C9.2, C10.2 (-), C12.2, C13.2, C14.2, C15.2 (-), C19.2, C20.2, D6.C, D8.C, IC2.2 (GND), IC3.2 (GND), IC6.3 (V-), IC7.3 (V-), R6.2, R8.1, R9.2, USBA_3-4.4 (GND), USBA_3-4.8 (GND); also elsewhere on the board
unnamed: IC2.5 (ILIM), R6.1
unnamed: IC3.5 (ILIM), R9.1
unnamed: D6.A, R18.1
unnamed: IC6.4 (OUT), R18.2, R20.1
unnamed: D5.C, R20.2
unnamed: D8.A, R21.1
unnamed: IC7.4 (OUT), R21.2, R23.1
unnamed: D7.C, R23.2
OCP3: IC2.4 (!FAULT), IC6.2 (IN), R19.1; also elsewhere on the board
OCP4: IC3.4 (!FAULT), IC7.2 (IN), R22.1; also elsewhere on the board
SHIELD: C1.1, R8.2, USBA_3-4.S1 (SHIELD), USBA_3-4.S2 (SHIELD), USBA_3-4.S3 (SHIELD), USBA_3-4.S4 (SHIELD); also elsewhere on the board
USBA3_EN: IC2.3 (EN), R7.2; also elsewhere on the board
USBA4_EN: IC3.3 (EN), R10.2; also elsewhere on the board
VBUS_USBA3: C8.1, C9.1, C10.1 (+), IC2.6 (OUT), USBA_3-4.1 (VBUS), VUSBA3.TP
VBUS_USBA4: C13.1, C14.1, C15.1 (+), IC3.6 (OUT), USBA_3-4.5 (VBUS), VUSBA4.TP

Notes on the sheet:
OUTPUT USB-A3
RLIM = 20kΩ = 1.2A
OUTPUT USB-A4
USB-A SOURCE PORT3-4
FAULT INDICATORS
